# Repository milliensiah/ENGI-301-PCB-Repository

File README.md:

# ENGI-301-PCB-Repository

Respository for ENGI 301 PCB

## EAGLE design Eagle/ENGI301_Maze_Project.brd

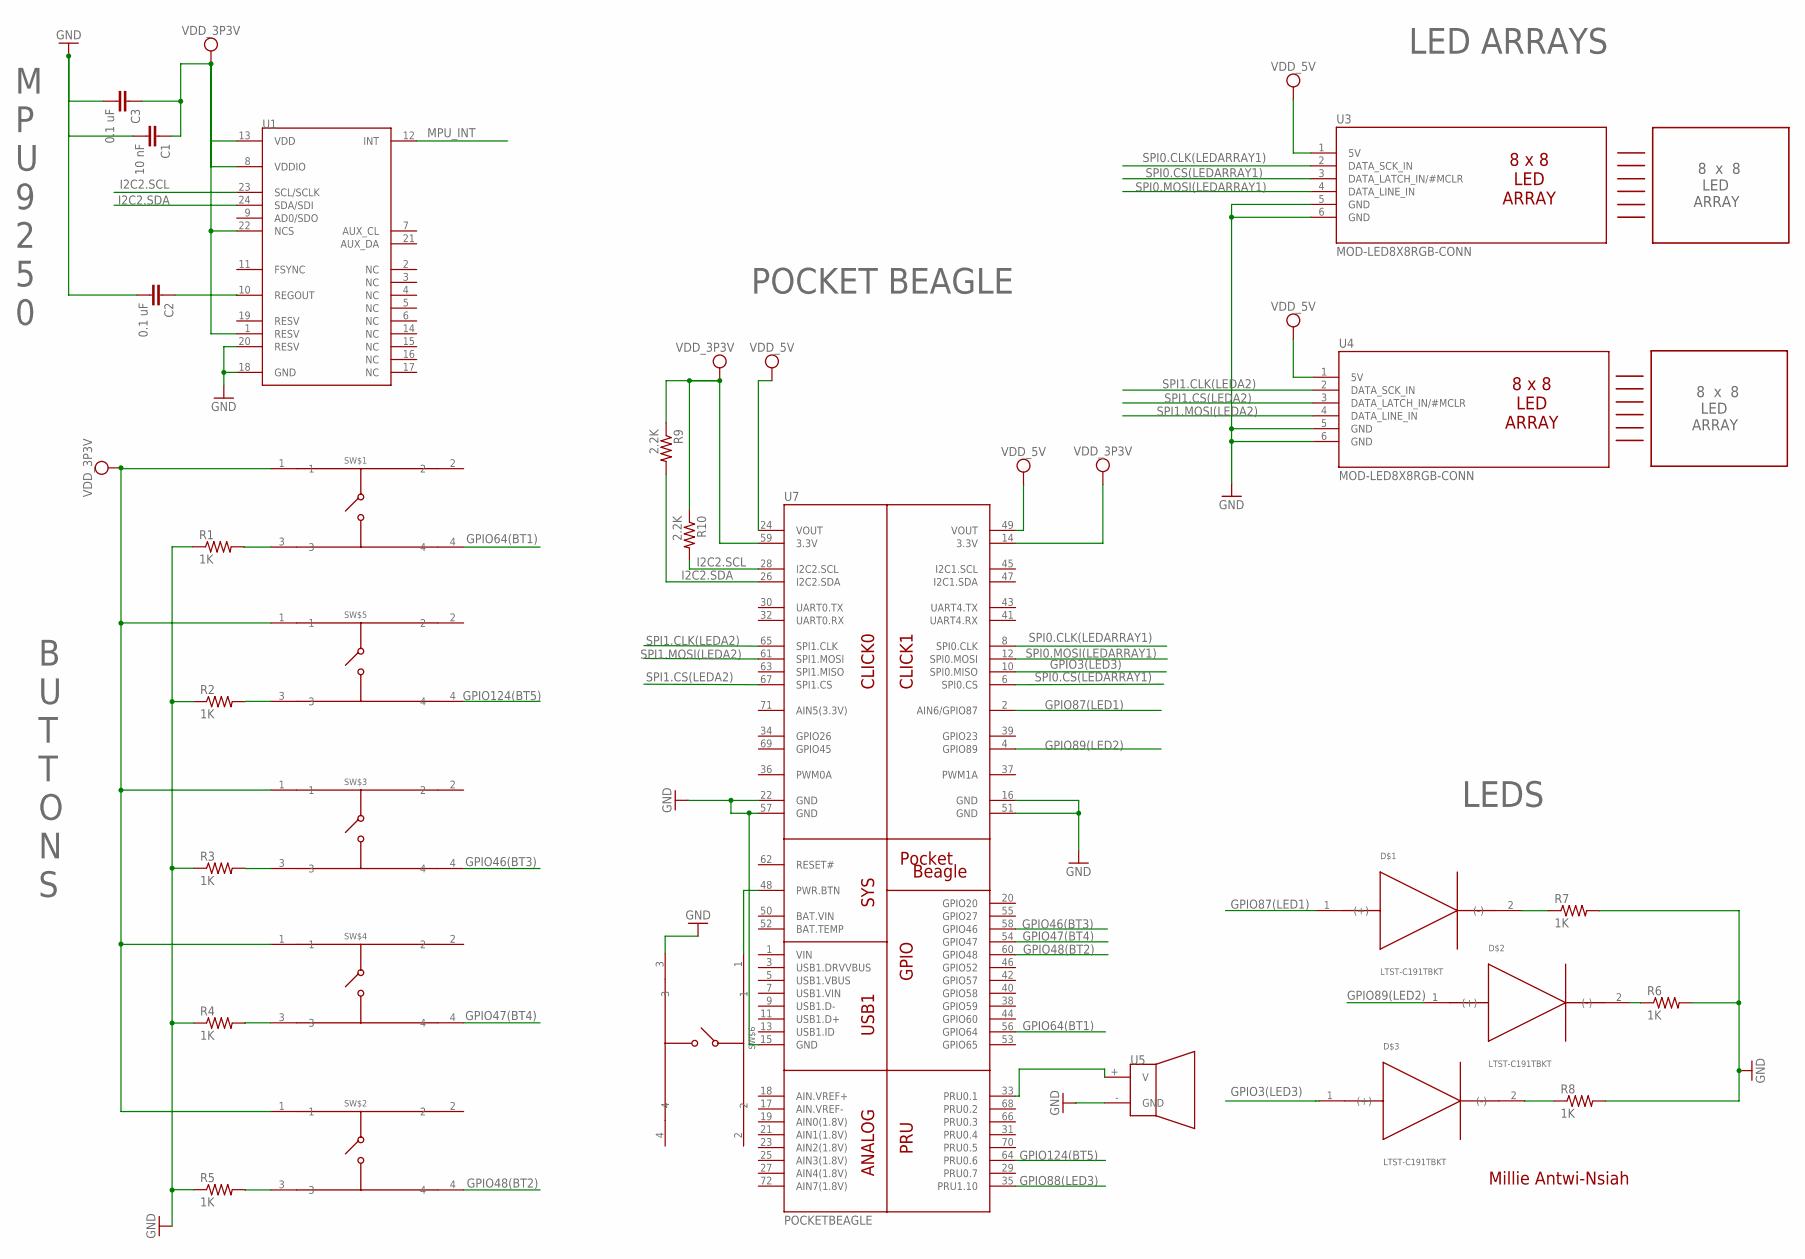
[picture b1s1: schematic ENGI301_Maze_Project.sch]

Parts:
C1: 10 nF; C0603
C2, C3: 0.1 uF; C0603
D$1, D$2, D$3: LTST-C191TBKT
R1, R2, R3, R4, R5, R6, R7, R8: 1K; R0603
R9, R10: 2.2K; R0603
SW$1, SW$2, SW$3, SW$4, SW$5, SW$6: TACTILE-BUTTON
U1: MPU-9250; QFN3MMX3MM
U3, U4: MOD-LED8X8RGB-CONN; FE06W
U5: CEM-1203
U7: POCKETBEAGLE

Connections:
GND: C1.2, C2.2, C3.2, R1.1, R2.1, R3.1, R4.1, R5.1, R7.2, R8.2, SW$6.3, U1.18 (GND), U1.20 (RESV), U3.5 (GND), U3.6 (GND), U4.5 (GND), U4.6 (GND), U5.- (GND), U7.16 (GND), U7.22 (GND), U7.51 (GND)
GPIO3(LED3): D$3.1 ((+)), U7.10 (SPI0.MISO)
GPIO46(BT3): SW$3.4, U7.58 (GPIO46)
GPIO47(BT4): SW$4.4, U7.54 (GPIO47)
GPIO48(BT2): SW$2.4, U7.60 (GPIO48)
GPIO64(BT1): SW$1.4, U7.56 (GPIO64)
GPIO87(LED1): D$1.1 ((+)), U7.2 (AIN6/GPIO87)
GPIO88(LED3): U7.35 (PRU1.10)
GPIO89(LED2): D$2.1 ((+)), U7.4 (GPIO89)
GPIO124(BT5): SW$5.4, U7.64 (PRU0.6)
I2C2.SCL: R10.2, U1.23 (SCL/SCLK), U7.28 (I2C2.SCL)
I2C2.SDA: R9.2, U1.24 (SDA/SDI), U7.26 (I2C2.SDA)
MPU_INT: U1.12 (INT)
unnamed: R5.2, SW$2.3
unnamed: R4.2, SW$4.3
unnamed: R3.2, SW$3.3
unnamed: R2.2, SW$5.3
unnamed: R1.2, SW$1.3
unnamed: D$1.2 ((-)), R7.1
unnamed: D$2.2 ((-)), R6.1
unnamed: D$3.2 ((-)), R8.1
unnamed: SW$6.1, U7.48 (PWR.BTN)
unnamed: U5.+ (V), U7.33 (PRU0.1)
unnamed: C2.1, U1.10 (REGOUT)
SPI0.CLK(LEDARRAY1): U3.2 (DATA_SCK_IN), U7.8 (SPI0.CLK)
SPI0.CS(LEDARRAY1): U3.3 (DATA_LATCH_IN/#MCLR), U7.6 (SPI0.CS)
SPI0.MOSI(LEDARRAY1): U3.4 (DATA_LINE_IN), U7.12 (SPI0.MOSI)
SPI1.CLK(LEDA2): U4.2 (DATA_SCK_IN), U7.65 (SPI1.CLK)
SPI1.CS(LEDA2): U4.3 (DATA_LATCH_IN/#MCLR), U7.67 (SPI1.CS)
SPI1.MOSI(LEDA2): U4.4 (DATA_LINE_IN), U7.61 (SPI1.MOSI)
SYS_VDD1_3P3V: C1.1, C3.1, R9.1, R10.1, SW$1.1, SW$2.1, SW$3.1, SW$4.1, SW$5.1, U1.1 (RESV), U1.8 (VDDIO), U1.13 (VDD), U1.22 (NCS), U7.14 (3.3V), U7.59 (3.3V)

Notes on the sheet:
8 x 8 LED ARRAY
LED ARRAYS
LEDS
POCKET BEAGLE
M P U 9 2 5 0
B U T T O N S
Millie Antwi-Nsiah

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
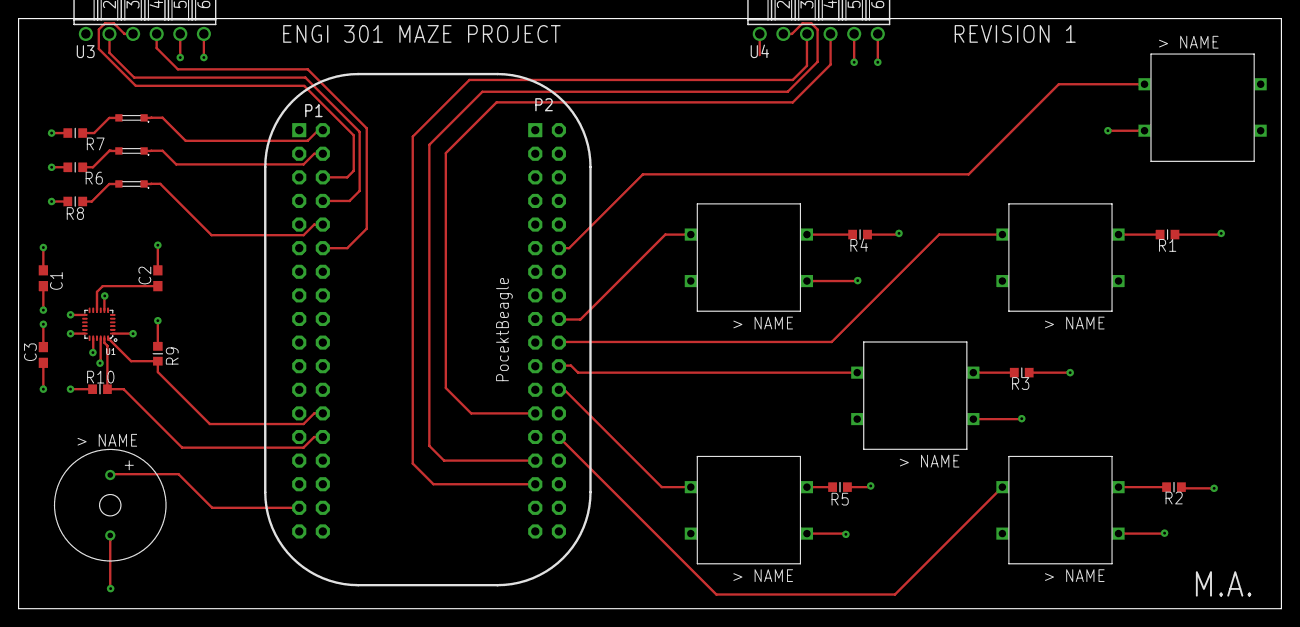
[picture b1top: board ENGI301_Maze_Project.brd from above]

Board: 4 copper layers, 135.9 x 63.5 mm, 27 parts (0 on the bottom side), 30 nets.

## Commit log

2018-04-07 Create Eagle
2018-04-07 Create PCB
2018-04-07 Create In-Class-Files
2018-04-07 Add files via upload
    Initial version of Eagle library from class
2018-04-09 Add files via upload
    Updated library with buzzer created and resistors imported
2018-04-09 Add files via upload
    Updated library with tactile button created
2018-04-09 ENGI 301 Library - Added SMD LED
    Library now includes MPU-9250, buzzer, LED, and button as well as imported capacitor, resistor, frame, GND, and VDD_3P3V
2018-04-20 Updated Maze Project Library
    - Fixed overlap issues with LED device
    - Fixed switched pins on the pocket beagle
    - Fixed name issues on LED, Buttons, and Buzzer
    - Added appropriate prefixes for each device
2018-04-20 Maze Project Schematic
2018-04-20 Maze Project Eagle Board
2018-04-20 Maze Project Eagle Board
    - Completed power and ground layers using ratsnest
2018-04-20 Maze Project Eagle Board
    - Power and ground planes completed using ratsnest
2018-04-20 Maze Project Eagle Schematic
    - Added my name to the title block in the frame
2018-04-20 PDF of Maze Project Eagle Schematic
2018-04-20 Maze Project Eagle Board
    -Properly connected 5 volt pins
2018-04-20 Create MFG_Directory
2018-04-20 Create MFG Files
2018-04-20 Maze Project Gerber Files
